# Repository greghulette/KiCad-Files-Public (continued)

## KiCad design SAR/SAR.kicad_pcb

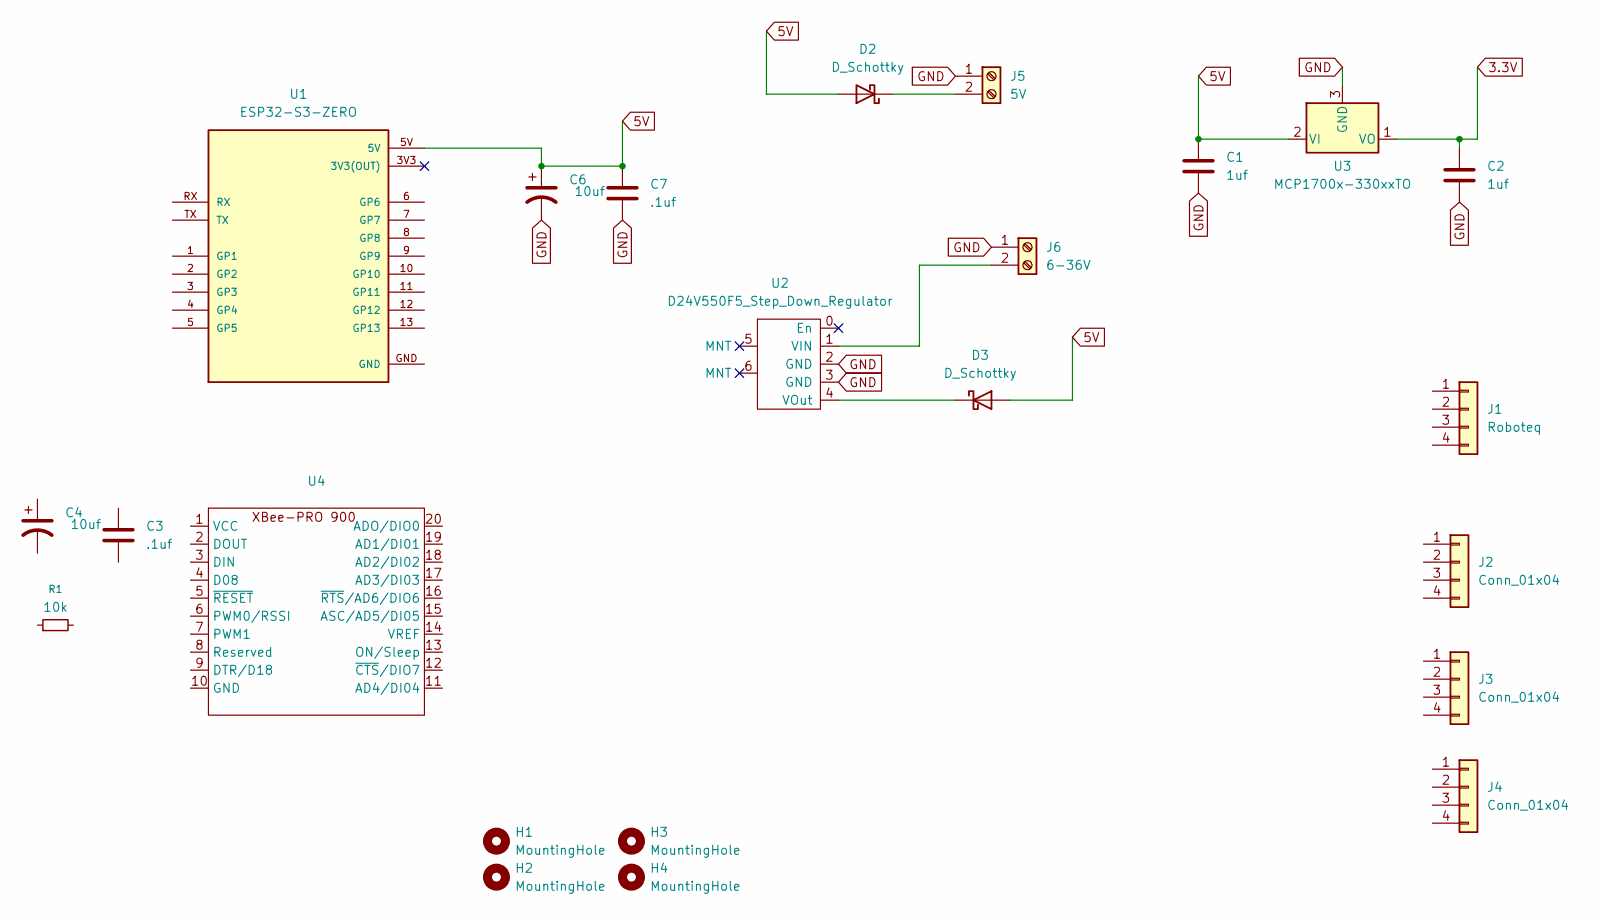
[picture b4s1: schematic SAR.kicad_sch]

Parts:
C1, C2: 1uf; C_Disc_D7.5mm_W4.4mm_P5.00mm
C3, C7: .1uf; C_Disc_D5.0mm_W2.5mm_P5.00mm
C4, C6: 10uf; CP_Radial_D5.0mm_P2.00mm
D2, D3: D_Schottky; D_DO-201AD_P12.70mm_Horizontal
H1, H2, H3, H4: MountingHole; MountingHole_3.2mm_M3
J1: Roboteq; PinHeader_1x04_P2.54mm_Vertical
J2, J3, J4: Conn_01x04; PinHeader_1x04_P2.54mm_Vertical
J5: 5V; TerminalBlock_Phoenix_MKDS-1,5-2-5.08_1x02_P5.08mm_Horizont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
J6: 6-36V; TerminalBlock_Phoenix_MKDS-1,5-2-5.08_1x02_P5.08mm_Horizont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
R1: 10k; R_Axial_DIN0207_L6.3mm_D2.5mm_P10.16mm_Horizontal
U1: ESP32-S3-ZERO; MODULE_ESP32-S3-ZERO; PARTREV NA
U2: D24V550F5_Step_Down_Regulator; D24V50F5_Step_Down_Regulator
U3: MCP1700x-330xxTO; TO-92_Inline
U4: XbeePro900

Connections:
3.3V: C2.1, U3.1 (VO)
5V: C1.1, C6.1, C7.1, D2.2 (A), D3.2 (A), U1.5V, U3.2 (VI)
GND: C1.2, C2.2, C6.2, C7.2, J5.1, J6.1, U2.2 (GND), U2.3 (GND), U3.3 (GND)
unnamed: D2.1 (K), J5.2
unnamed: D3.1 (K), U2.4 (VOut)
unnamed: J6.2, U2.1 (VIN)

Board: 2 copper layers, 23 parts (0 on the bottom side), 6 nets, no tracks yet.

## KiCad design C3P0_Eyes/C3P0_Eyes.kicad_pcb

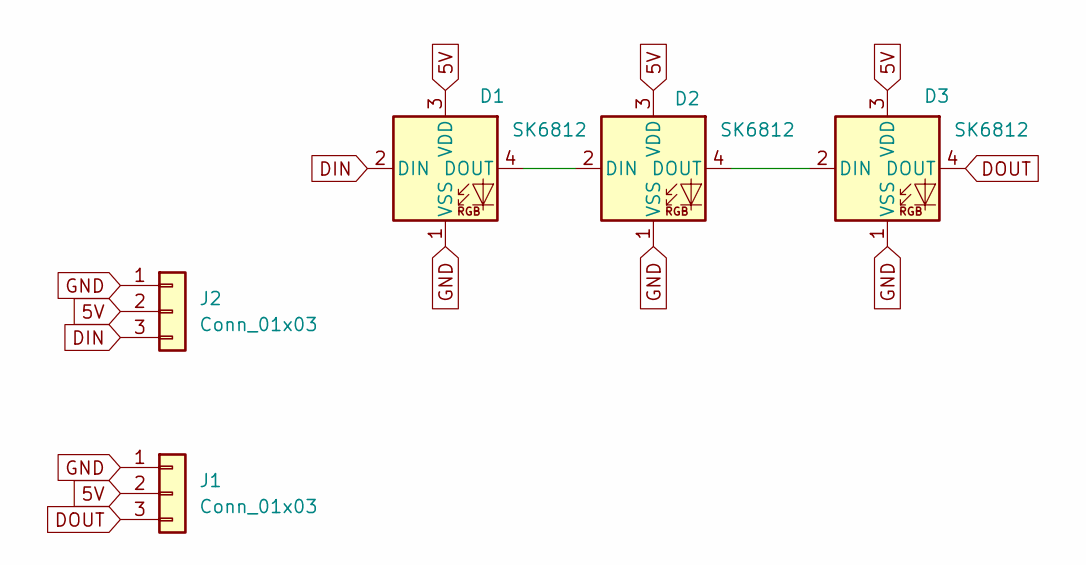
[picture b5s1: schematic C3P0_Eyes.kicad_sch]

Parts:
D1, D2, D3: SK6812; LED_SK6812_PLCC4_5.0x5.0mm_P3.2mm; LCSC C5378724
J1, J2: Conn_01x03; PinHeader_1x03_P2.54mm_Vertical; LCSC C24980

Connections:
5V: D1.3 (VDD), D2.3 (VDD), D3.3 (VDD), J1.2, J2.2
DIN: D1.2 (DIN), J2.3
DOUT: D3.4 (DOUT), J1.3
GND: D1.1 (VSS), D2.1 (VSS), D3.1 (VSS), J1.1, J2.1
unnamed: D1.4 (DOUT), D2.2 (DIN)
unnamed: D2.4 (DOUT), D3.2 (DIN)

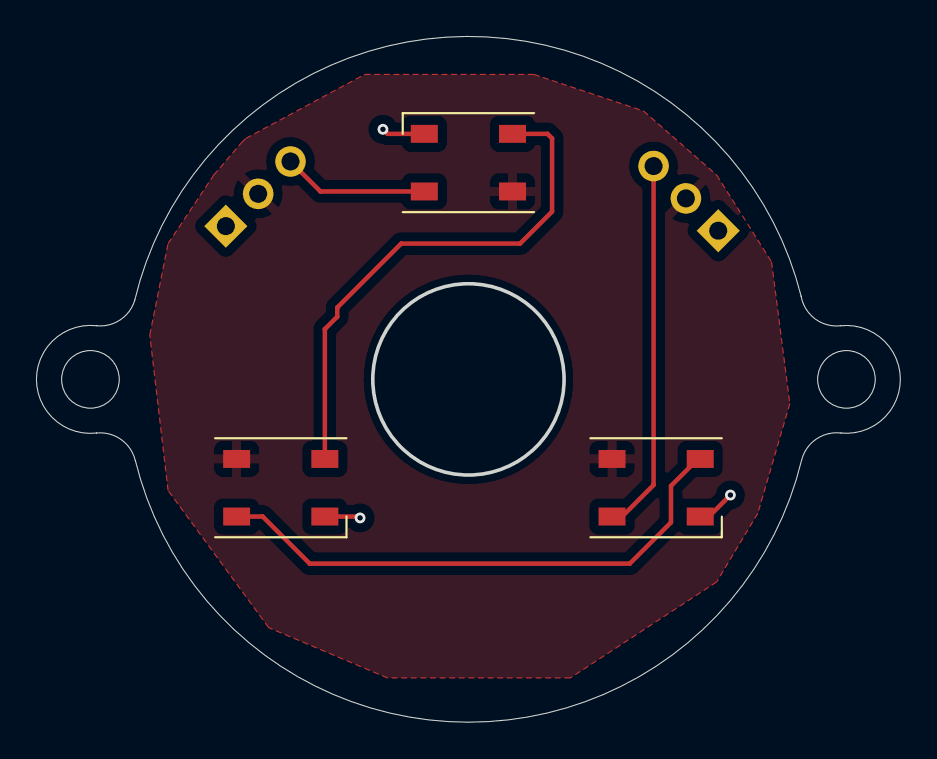
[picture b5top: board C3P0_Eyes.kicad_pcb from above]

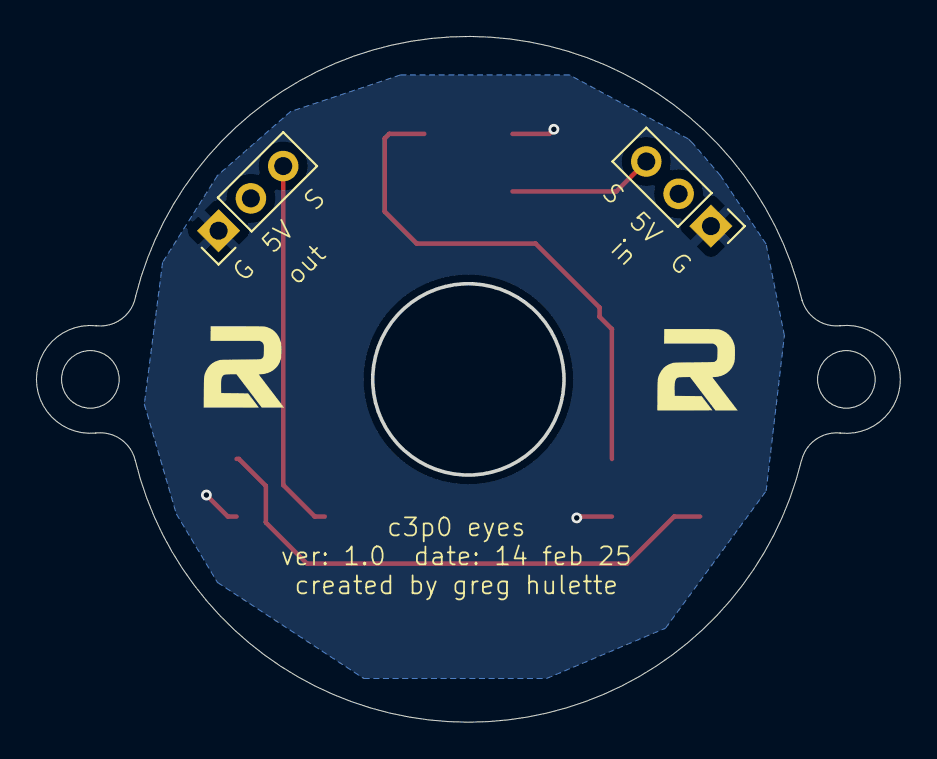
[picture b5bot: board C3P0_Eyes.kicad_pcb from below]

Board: 2 copper layers, 48.0 x 38.1 mm, 5 parts (2 on the bottom side), 6 nets.

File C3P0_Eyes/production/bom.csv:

Designator,Footprint,Quantity,Value,LCSC Part #
"D1, D2, D3",LED_SK6812_PLCC4_5.0x5.0mm_P3.2mm,3,SK6812,C5378724
"J1, J2",PinHeader_1x03_P2.54mm_Vertical,2,Conn_01x03,C24980

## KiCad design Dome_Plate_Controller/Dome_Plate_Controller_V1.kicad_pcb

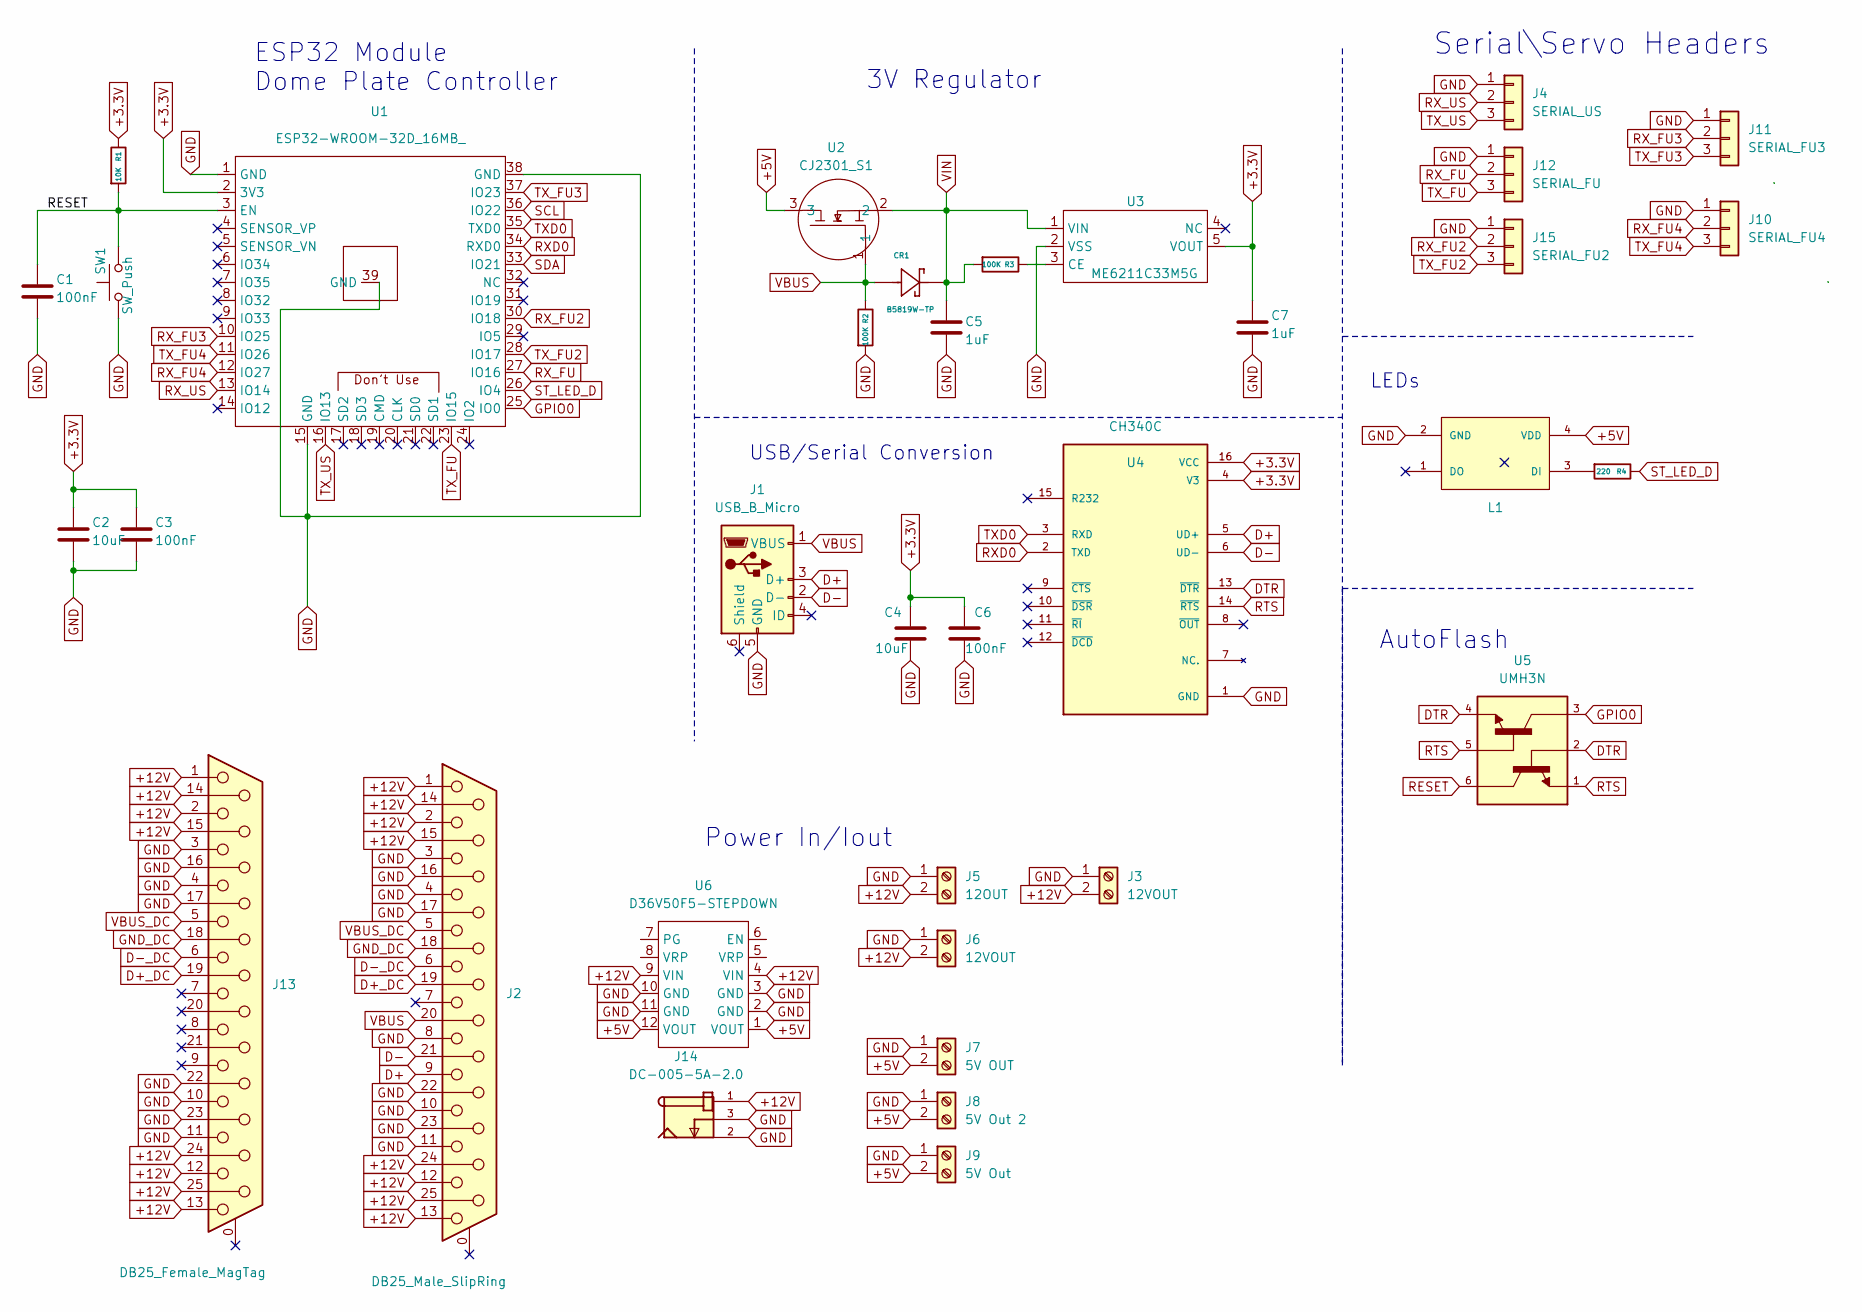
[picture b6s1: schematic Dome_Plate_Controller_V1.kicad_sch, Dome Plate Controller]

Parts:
C1, C3, C6: 100nF; C_0402_1005Metric; LCSC C307331
C2, C4: 10uF; C_0402_1005Metric; LCSC C315248
C5, C7: 1uF; C_0402_1005Metric; LCSC C77009
CR1: B5819W-TP; SOD3716X135N; LCSC C84354
J1: USB_B_Micro; USB_Micro-B_Amphenol_10118194_Horizontal; LCSC C132563
J2: DB25_Male_SlipRing; DSUB-25_Male_Vertical_P2.77x2.84mm_MountingHoles; LCSC C2984302
J3, J6: 12VOUT; TerminalBlock_4Ucon_1x02_P3.50mm_Horizontal; LCSC C474892
J4: SERIAL_US; Molex_KK-254_AE-6410-03A_1x03_P2.54mm_Vertical; LCSC C471416
J5: 12OUT; TerminalBlock_4Ucon_1x02_P3.50mm_Horizontal; LCSC C474892
J7: 5V OUT; TerminalBlock_4Ucon_1x02_P3.50mm_Horizontal; LCSC C474892
J8: 5V Out 2; TerminalBlock_4Ucon_1x02_P3.50mm_Horizontal; LCSC C474892
J9: 5V Out; TerminalBlock_4Ucon_1x02_P3.50mm_Horizontal; LCSC C474892
J10: SERIAL_FU4; Molex_KK-254_AE-6410-03A_1x03_P2.54mm_Vertical; LCSC C471416
J11: SERIAL_FU3; Molex_KK-254_AE-6410-03A_1x03_P2.54mm_Vertical; LCSC C471416
J12: SERIAL_FU; Molex_KK-254_AE-6410-03A_1x03_P2.54mm_Vertical; LCSC C471416
J13: DB25_Female_MagTag; DSUB-25_Female_Vertical_P2.77x2.84mm_MountingHoles; LCSC C2938621
J14: DC-005-5A-2.0; XKB_DC-005-5A-2.0; PARTREV A0; LCSC C3010535
J15: SERIAL_FU2; Molex_KK-254_AE-6410-03A_1x03_P2.54mm_Vertical; LCSC C471416
L1: WS2812B-2020; LCSC C965555
R1: 10K; R_0603_1608Metric; LCSC C269701
R2, R3: 100K; R_0603_1608Metric; LCSC C25803
R4: 220; R_0402_1005Metric; LCSC C25091
SW1: SW_Push; TS-1101S-B-B-B-W-A; LCSC C692465
U1: ESP32-WROOM-32D_16MB_; ESP32-WROOM-32; LCSC C529578
U2: CJ2301_S1; SOT-23; LCSC C8547
U3: ME6211C33M5G; SOT-23-5; LCSC C82942
U4: CH340C; SOIC127P600X180-16N; PARTREV 2G; LCSC C84681
U5: UMH3N; UMT6; LCSC C62892
U6: D36V50F5-STEPDOWN

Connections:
+3.3V: C2.1, C3.1, C4.1, C6.1, C7.1, R1.1, U1.2 (3V3), U3.5 (VOUT), U4.4 (V3), U4.16 (VCC)
+5V: J7.2, J8.2, J9.2, L1.4 (VDD), U2.3, U6.1 (VOUT), U6.12 (VOUT)
+12V: J2.1, J2.2, J2.12, J2.13, J2.14, J2.15, J2.24, J2.25, J3.2, J5.2, J6.2, J13.1, J13.2, J13.12, J13.13, J13.14, J13.15, J13.24, J13.25, J14.1, U6.4 (VIN), U6.9 (VIN)
D+: J1.3 (D+), J2.9, U4.5 (UD+)
D+_DC: J2.19, J13.19
D-: J1.2 (D-), J2.21, U4.6 (UD-)
D-_DC: J2.6, J13.6
DTR: U4.13 (~DTR), U5.2, U5.4
GND: C1.2, C2.2, C3.2, C4.2, C5.1, C6.2, C7.2, J1.5 (GND), J2.3, J2.4, J2.8, J2.10, J2.11, J2.16, J2.17, J2.22, J2.23, J3.1, J4.1, J5.1, J6.1, J7.1, J8.1, J9.1, J10.1, J11.1, J12.1, J13.3, J13.4, J13.10, J13.11, J13.16, J13.17, J13.22, J13.23, J14.2, J14.3, J15.1, L1.2 (VSS), R2.2, SW1.1, U1.1 (GND), U1.15 (GND), U1.38 (GND), U1.39 (GND), U3.2 (VSS), U4.1 (GND), U6.2 (GND), U6.3 (GND), U6.10 (GND), U6.11 (GND)
GND_DC: J2.18, J13.18
GPIO0: U1.25 (IO0), U5.3
unnamed: L1.3 (DI), R4.2
unnamed: R3.1, U3.3 (CE)
RESET: C1.1, R1.2, SW1.2, U1.3 (EN), U5.6
RTS: U4.14 (~RTS), U5.1, U5.5
RXD0: U1.34 (RXD0), U4.2 (TXD)
RX_FU: J12.2, U1.27 (IO16)
RX_FU2: J15.2, U1.30 (IO18)
RX_FU3: J11.2, U1.10 (IO25)
RX_FU4: J10.2, U1.12 (IO27)
RX_US: J4.2, U1.13 (IO14)
SCL: U1.36 (IO22)
SDA: U1.33 (IO21)
ST_LED_D: R4.1, U1.26 (IO4)
TXD0: U1.35 (TXD0), U4.3 (RXD)
TX_FU: J12.3, U1.23 (IO15)
TX_FU2: J15.3, U1.28 (IO17)
TX_FU3: J11.3, U1.37 (IO23)
TX_FU4: J10.3, U1.11 (IO26)
TX_US: J4.3, U1.16 (IO13)
VBUS: CR1.A, J1.1 (VBUS), J2.20, R2.1, U2.1
VBUS_DC: J2.5, J13.5
VIN: C5.2, CR1.C, R3.2, U2.2, U3.1 (VIN)

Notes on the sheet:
ESP32 Module Dome Plate Controller
3V Regulator
LEDs
Power In/Iout
USB/Serial Conversion
AutoFlash
Serial\Servo Headers

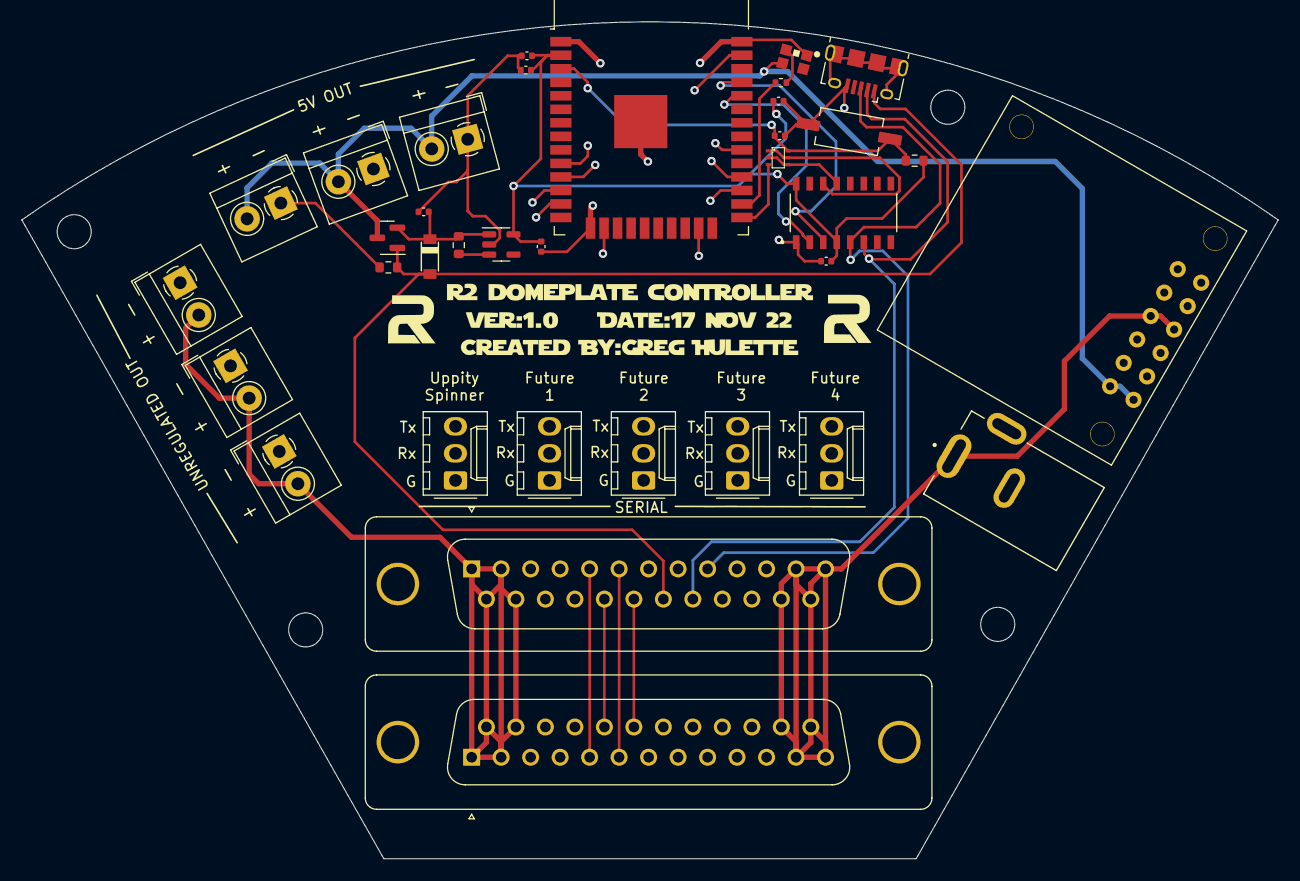
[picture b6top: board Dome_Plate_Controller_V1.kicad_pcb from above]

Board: 4 copper layers, 118.0 x 78.6 mm, 35 parts (0 on the bottom side), 31 nets.

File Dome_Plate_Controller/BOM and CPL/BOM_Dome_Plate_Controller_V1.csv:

Comment,Designator,Footprint,LCSC
100nF,"C1,C3,C6",Capacitor_SMD:C_0402_1005Metric,C307331
10uF,"C2,C4",Capacitor_SMD:C_0402_1005Metric,C315248
1uF,"C5,C7",Capacitor_SMD:C_0402_1005Metric,C77009
B5819W-TP,CR1,Custom:SOD3716X135N,C84354
USB_B_Micro,J1,Connector_USB:USB_Micro-B_Amphenol_10118194_Horizontal,C132563
SERIAL_FU4,J10,Connector_Molex:Molex_KK-254_AE-6410-03A_1x03_P2.54mm_Vertical,C471416
SERIAL_FU3,J11,Connector_Molex:Molex_KK-254_AE-6410-03A_1x03_P2.54mm_Vertical,C471416
SERIAL_FU,J12,Connector_Molex:Molex_KK-254_AE-6410-03A_1x03_P2.54mm_Vertical,C471416
DB25_Female_MagTag,J13,Connector_Dsub:DSUB-25_Female_Vertical_P2.77x2.84mm_MountingHoles,C2938621
DC-005-5A-2.0,J14,Custom:XKB_DC-005-5A-2.0,C3010535
SERIAL_FU2,J15,Connector_Molex:Molex_KK-254_AE-6410-03A_1x03_P2.54mm_Vertical,C471416
DB25_Male_SlipRing,J2,Connector_Dsub:DSUB-25_Male_Vertical_P2.77x2.84mm_MountingHoles,C2984302
12VOUT,"J3,J6",TerminalBlock_4Ucon:TerminalBlock_4Ucon_1x02_P3.50mm_Horizontal, C474892
SERIAL_US,J4,Connector_Molex:Molex_KK-254_AE-6410-03A_1x03_P2.54mm_Vertical,C471416
12OUT,J5,TerminalBlock_4Ucon:TerminalBlock_4Ucon_1x02_P3.50mm_Horizontal, C474892
5V OUT,J7,TerminalBlock_4Ucon:TerminalBlock_4Ucon_1x02_P3.50mm_Horizontal, C474892
5V Out 2,J8,TerminalBlock_4Ucon:TerminalBlock_4Ucon_1x02_P3.50mm_Horizontal, C474892
5V Out,J9,TerminalBlock_4Ucon:TerminalBlock_4Ucon_1x02_P3.50mm_Horizontal, C474892
WS2812B-2020,L1,WS2812B-2020,C965555
10K,R1,Resistor_SMD:R_0603_1608Metric,C269701
100K,"R2,R3",Resistor_SMD:R_0603_1608Metric,C25803
220,R4,Resistor_SMD:R_0402_1005Metric,C25091
SW_Push,SW1,Custom:TS-1101S-B-B-B-W-A, C692465
ESP32-WROOM-32D_16MB_,U1,RF_Module:ESP32-WROOM-32, C529578
CJ2301_S1,U2,Package_TO_SOT_SMD:SOT-23, C8547
ME6211C33M5G,U3,Package_TO_SOT_SMD:SOT-23-5,C82942
CH340C,U4,Custom:SOIC127P600X180-16N,C84681
UMH3N,U5,Custom:UMT6, C62892
